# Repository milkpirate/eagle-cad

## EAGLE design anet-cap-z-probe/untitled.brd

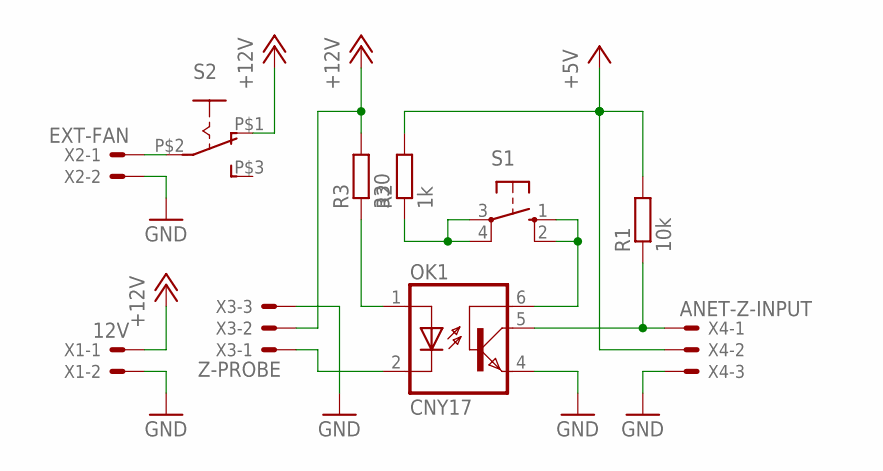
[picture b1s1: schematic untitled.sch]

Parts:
OK1: CNY17; DIL06
R1: 10k; M0805
R2: 1k; M0805
R3: 330; M0805
S1: 10-XX; B3F-10XX
S2: EG1218THIN; THIN
X1: 12V; JST-XH-02-PACKAGE-LONG-PAD
X2: EXT-FAN; JST-XH-02-PACKAGE-LONG-PAD
X3: Z-PROBE; JST-XH-03-PACKAGE-LONG-PAD
X4: ANET-Z-INPUT; JST-XH-03-PACKAGE-LONG-PAD

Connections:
+5V: R1.2, R2.2, X4.2
+12V: R3.2, S2.P$1 (O), X1.1, X3.2
GND: OK1.4 (EMI), X1.2, X2.2, X3.3, X4.3
unnamed: S2.P$2, X2.1
unnamed: OK1.5 (COL), R1.1, X4.1
unnamed: R2.1, S1.3, S1.4 (P1)
unnamed: OK1.6 (BAS), S1.1 (S), S1.2 (S1)
unnamed: OK1.1 (A), R3.1
unnamed: OK1.2 (C), X3.1

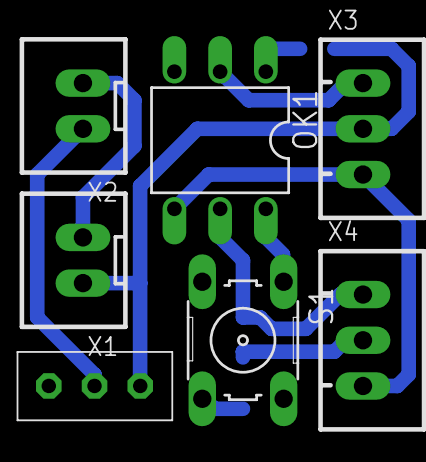
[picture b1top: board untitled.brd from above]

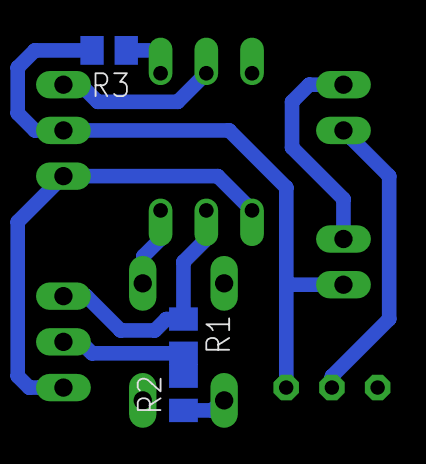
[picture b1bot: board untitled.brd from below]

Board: 2 copper layers, 10 parts (3 on the bottom side), 9 nets.

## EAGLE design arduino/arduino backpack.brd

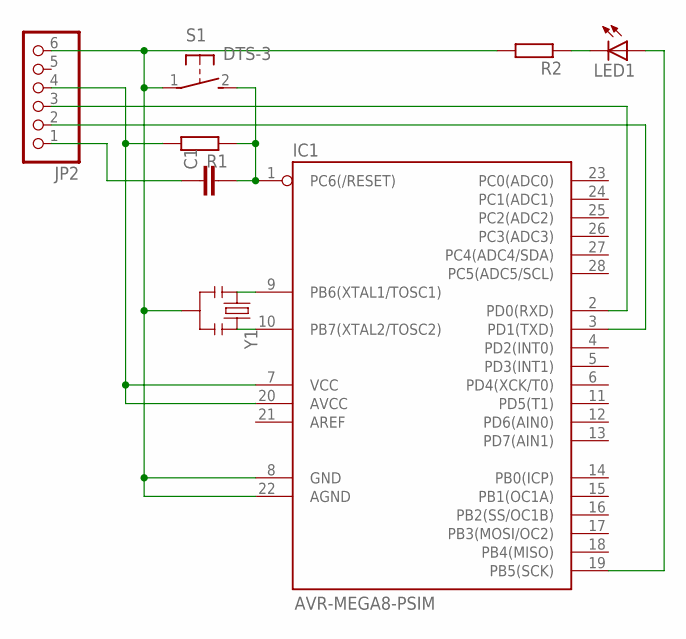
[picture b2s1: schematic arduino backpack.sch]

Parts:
C1: C-EU025-025X050; C025-025X050
IC1: AVR-MEGA8-PSIM; DIL28-3-SIMON
JP2: PINHD-1X6; 1X06
LED1: LED3MM
R1, R2: R-EU_0204/2V; 0204V
S1: DTS-3
Y1: RESONATORPTH; RESONATOR-PTH

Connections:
unnamed: IC1.8 (GND), IC1.22 (AGND), JP2.6, R2.2, S1.1, Y1.2
unnamed: IC1.7 (VCC), IC1.20 (AVCC), JP2.4, R1.2
unnamed: IC1.2 (PD0(RXD)), JP2.3
unnamed: IC1.3 (PD1(TXD)), JP2.2
unnamed: C1.1, JP2.1
unnamed: C1.2, IC1.1 (PC6(/RESET)), R1.1, S1.2
unnamed: IC1.9 (PB6(XTAL1/TOSC1)), Y1.1
unnamed: IC1.10 (PB7(XTAL2/TOSC2)), Y1.3
unnamed: LED1.K (C), R2.1
unnamed: IC1.19 (PB5(SCK)), LED1.A

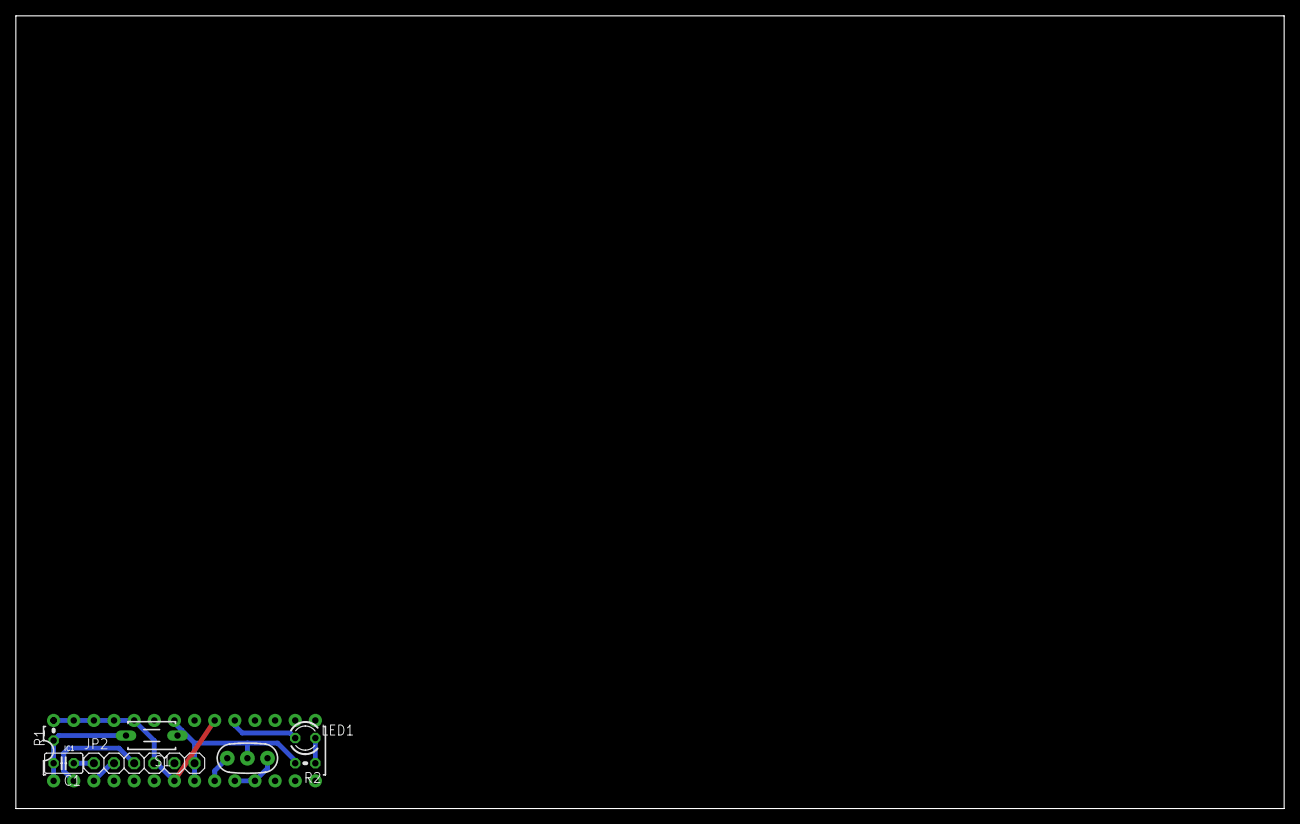
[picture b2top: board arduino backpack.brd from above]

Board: 2 copper layers, 160.0 x 100.0 mm, 8 parts (0 on the bottom side), 10 nets.

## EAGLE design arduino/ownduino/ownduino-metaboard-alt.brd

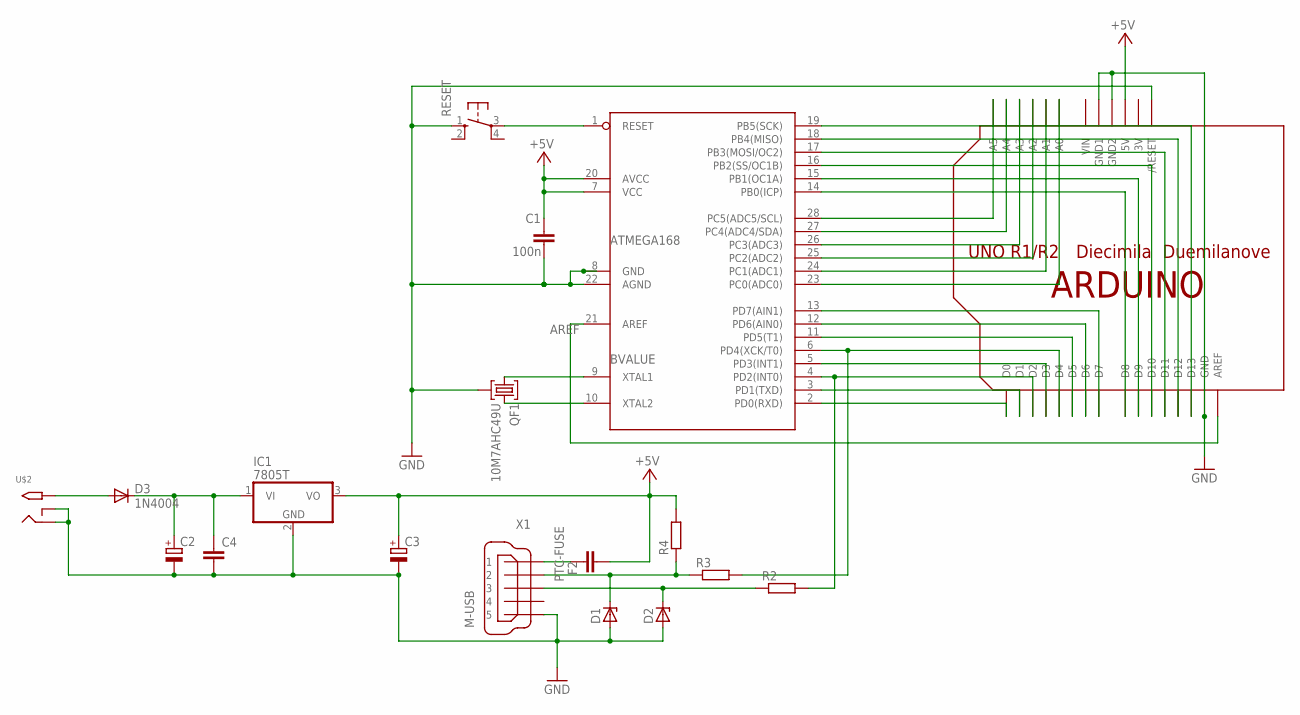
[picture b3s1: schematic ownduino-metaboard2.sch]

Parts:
BVALUE: ATMEGA168; DIL28-3
C1: 100n; C025-024X044
C2, C3: CPOL-EUE5-8.5; E5-8,5
C4: C-EU025-025X050; C025-025X050
D1: ZENER-DIODEZD-7.5; ZDIO-7.5
D2: ZENER-DIODEZD-5; ZDIO-5
D3: 1N4004; DO41-10
F2: PTC-FUSE; C025_050-025X075
IC1: 7805T; TO220H
QF1: 10M7AHC49U; HC49U
R2: R-EU_0207/12; 0207/12
R3, R4: R-EU_0207/10; 0207/10
RESET: 10-XX; B3F-10XX
U$1: ARDUINOUNO; ARDUINO
U$2: 2.1MMJACKTHM; PJ-102A
X1: M-USB; 32005-601

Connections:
3V: U$1.3V
+5V: BVALUE.7 (VCC), BVALUE.20 (AVCC), C1.1, C3.+, F2.1, IC1.3 (VO), R4.2, U$1.5V
A0: BVALUE.23 (PC0(ADC0)), U$1.A0
A1: BVALUE.24 (PC1(ADC1)), U$1.A1
A2: BVALUE.25 (PC2(ADC2)), U$1.A2
A3: BVALUE.26 (PC3(ADC3)), U$1.A3
A4: BVALUE.27 (PC4(ADC4/SDA)), U$1.A4
A5: BVALUE.28 (PC5(ADC5/SCL)), U$1.A5
AREF: BVALUE.21 (AREF), U$1.AREF
D0: BVALUE.2 (PD0(RXD)), U$1.D0
D1: BVALUE.3 (PD1(TXD)), U$1.D1
D2: BVALUE.4 (PD2(INT0)), R2.2, U$1.D2
D3: BVALUE.5 (PD3(INT1)), U$1.D3
D4: BVALUE.6 (PD4(XCK/T0)), R3.2, U$1.D4
D5: BVALUE.11 (PD5(T1)), U$1.D5
D6: BVALUE.12 (PD6(AIN0)), U$1.D6
D7: BVALUE.13 (PD7(AIN1)), U$1.D7
D8: BVALUE.14 (PB0(ICP)), U$1.D8
D9: BVALUE.15 (PB1(OC1A)), U$1.D9
D10: BVALUE.16 (PB2(SS/OC1B)), U$1.D10
D11-MOSI: BVALUE.17 (PB3(MOSI/OC2)), U$1.D11
D12-MISO: BVALUE.18 (PB4(MISO)), U$1.D12
D13-SCK: BVALUE.19 (PB5(SCK)), U$1.D13
D+: D2.C, R2.1, X1.3
D-: D1.C, R3.1, R4.1, X1.2
GND: BVALUE.8 (GND), BVALUE.22 (AGND), C1.2, C2.-, C3.-, C4.2, D1.A, D2.A, IC1.2 (GND), QF1.2, RESET.1 (S), U$1.GND, U$1.GND1, U$1.GND2, U$1.RESET (/RESET), U$2.RING, U$2.RING_SW, X1.5
unnamed: BVALUE.1 (RESET), RESET.3
unnamed: C2.+, C4.1, D3.C, IC1.1 (VI)
unnamed: D3.A, U$2.TIP
unnamed: BVALUE.9 (XTAL1), QF1.1
unnamed: BVALUE.10 (XTAL2), QF1.3
unnamed: F2.2, X1.1
VIN: U$1.VIN

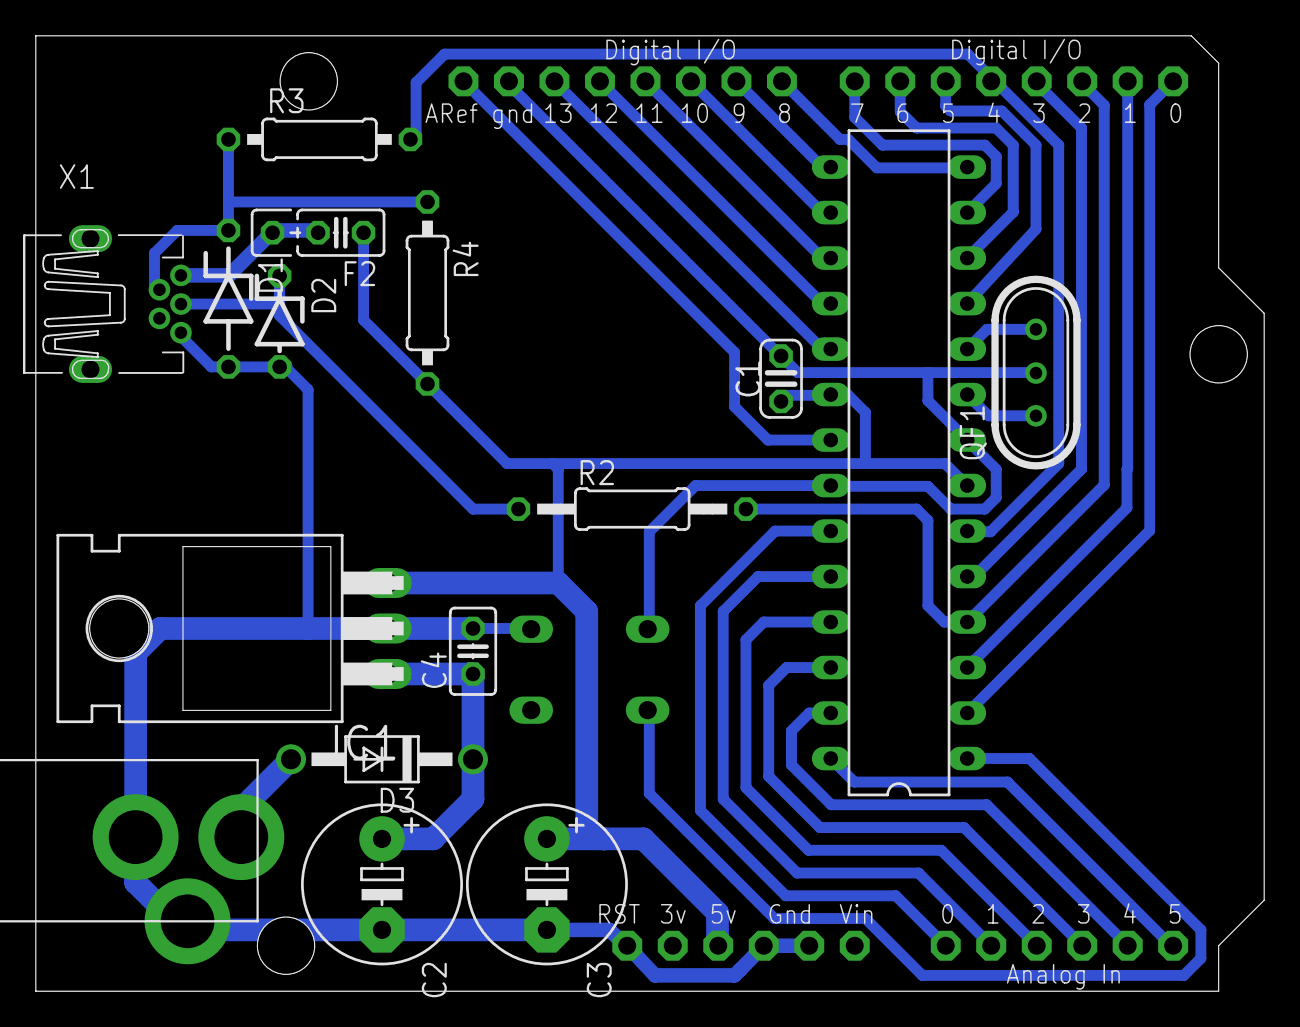
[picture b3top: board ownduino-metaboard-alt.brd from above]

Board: 2 copper layers, 68.6 x 53.3 mm, 18 parts (1 on the bottom side), 31 nets.

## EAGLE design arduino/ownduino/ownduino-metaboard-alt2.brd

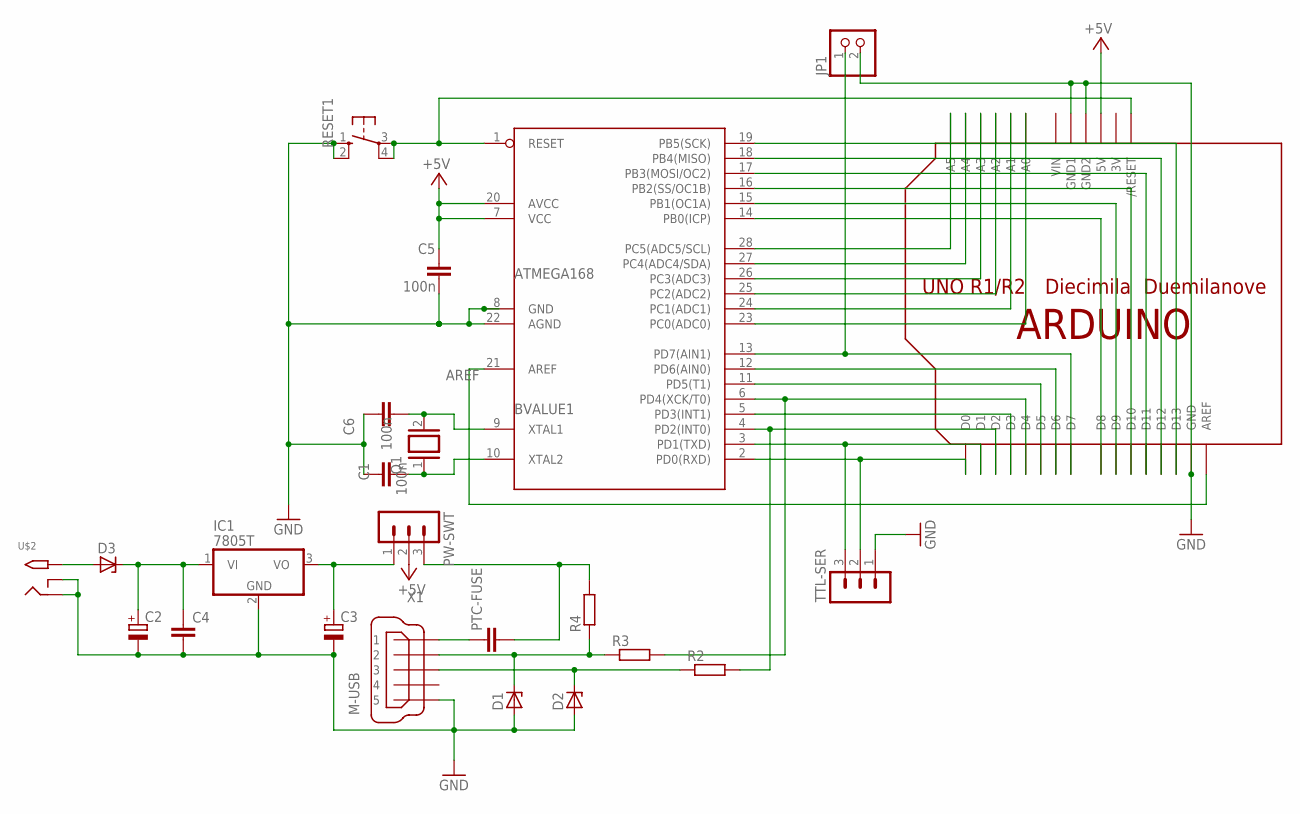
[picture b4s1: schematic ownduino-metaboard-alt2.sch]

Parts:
BVALUE1: ATMEGA168; DIL28-3
C1, C5, C6: 100n; C025-024X044
C2, C3: CPOL-EUE2.5-6; E2,5-6
C4: C-EU025-025X050; C025-025X050
D1, D3: ZENER-DIODEZD-7.5; ZDIO-7.5
D2: ZENER-DIODEZD-5; ZDIO-5
IC1: 7805T; TO220H
JP1: PINHD-1X2; 1X02
PTC-FUSE: C-EU025_050-025X075; C025_050-025X075
PW-SWT: MA03-1
Q1: XTAL/S; QS
R2: R-EU_0207/12; 0207/12
R3, R4: R-EU_0207/10; 0207/10
RESET1: 10-XX; B3F-10XX
TTL-SER: MA03-1
U$1: ARDUINOUNO; ARDUINO
U$2: 2.1MMJACKTHM; PJ-102A
X1: M-USB; 32005-601

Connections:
3V: U$1.3V
+5V: BVALUE1.7 (VCC), BVALUE1.20 (AVCC), C5.1, PW-SWT.2, U$1.5V
A0: BVALUE1.23 (PC0(ADC0)), U$1.A0
A1: BVALUE1.24 (PC1(ADC1)), U$1.A1
A2: BVALUE1.25 (PC2(ADC2)), U$1.A2
A3: BVALUE1.26 (PC3(ADC3)), U$1.A3
A4: BVALUE1.27 (PC4(ADC4/SDA)), U$1.A4
A5: BVALUE1.28 (PC5(ADC5/SCL)), U$1.A5
AREF: BVALUE1.21 (AREF), U$1.AREF
D0: BVALUE1.2 (PD0(RXD)), TTL-SER.2, U$1.D0
D1: BVALUE1.3 (PD1(TXD)), TTL-SER.3, U$1.D1
D2: BVALUE1.4 (PD2(INT0)), R2.2, U$1.D2
D3: BVALUE1.5 (PD3(INT1)), U$1.D3
D4: BVALUE1.6 (PD4(XCK/T0)), R3.2, U$1.D4
D5: BVALUE1.11 (PD5(T1)), U$1.D5
D6: BVALUE1.12 (PD6(AIN0)), U$1.D6
D7: BVALUE1.13 (PD7(AIN1)), JP1.1, U$1.D7
D8: BVALUE1.14 (PB0(ICP)), U$1.D8
D9: BVALUE1.15 (PB1(OC1A)), U$1.D9
D10: BVALUE1.16 (PB2(SS/OC1B)), U$1.D10
D11-MOSI: BVALUE1.17 (PB3(MOSI/OC2)), U$1.D11
D12-MISO: BVALUE1.18 (PB4(MISO)), U$1.D12
D13-SCK: BVALUE1.19 (PB5(SCK)), U$1.D13
D+: D2.C, R2.1, X1.3
D-: D1.C, R3.1, R4.1, X1.2
GND: BVALUE1.8 (GND), BVALUE1.22 (AGND), C1.1, C2.-, C3.-, C4.2, C5.2, C6.1, D1.A, D2.A, IC1.2 (GND), JP1.2, RESET1.1 (S), RESET1.2 (S1), TTL-SER.1, U$1.GND, U$1.GND1, U$1.GND2, U$2.RING, U$2.RING_SW, X1.5
unnamed: C3.+, IC1.3 (VO), PW-SWT.1
unnamed: C2.+, C4.1, D3.C, IC1.1 (VI)
unnamed: D3.A, U$2.TIP
unnamed: BVALUE1.9 (XTAL1), C6.2, Q1.2
unnamed: BVALUE1.10 (XTAL2), C1.2, Q1.1
unnamed: PTC-FUSE.2, PW-SWT.3, R4.2
unnamed: BVALUE1.1 (RESET), RESET1.3, RESET1.4 (P1), U$1.RESET (/RESET)
unnamed: PTC-FUSE.1, X1.1
VIN: U$1.VIN

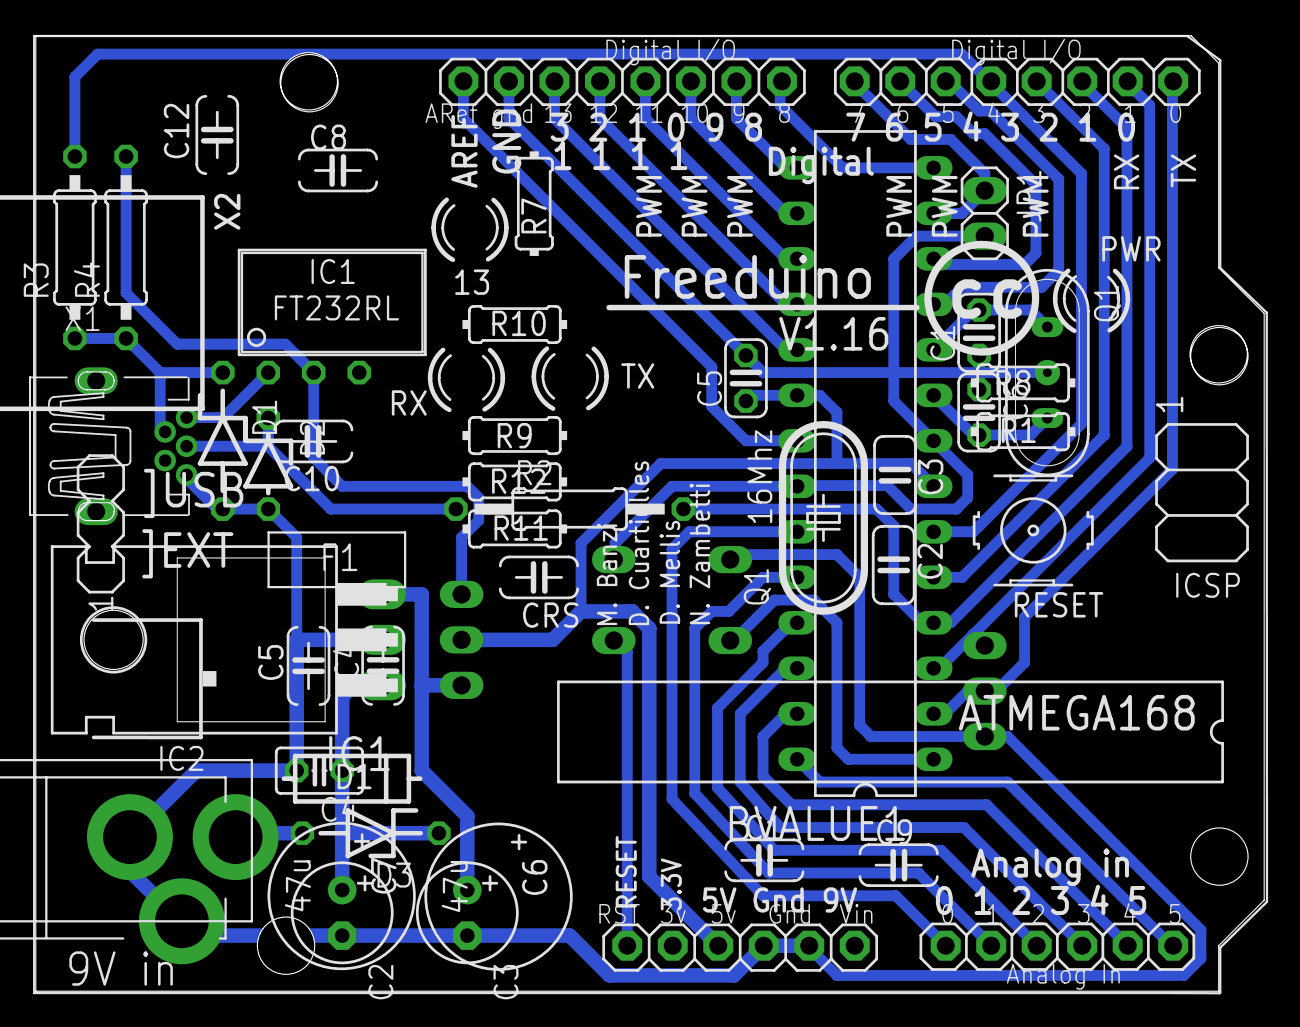
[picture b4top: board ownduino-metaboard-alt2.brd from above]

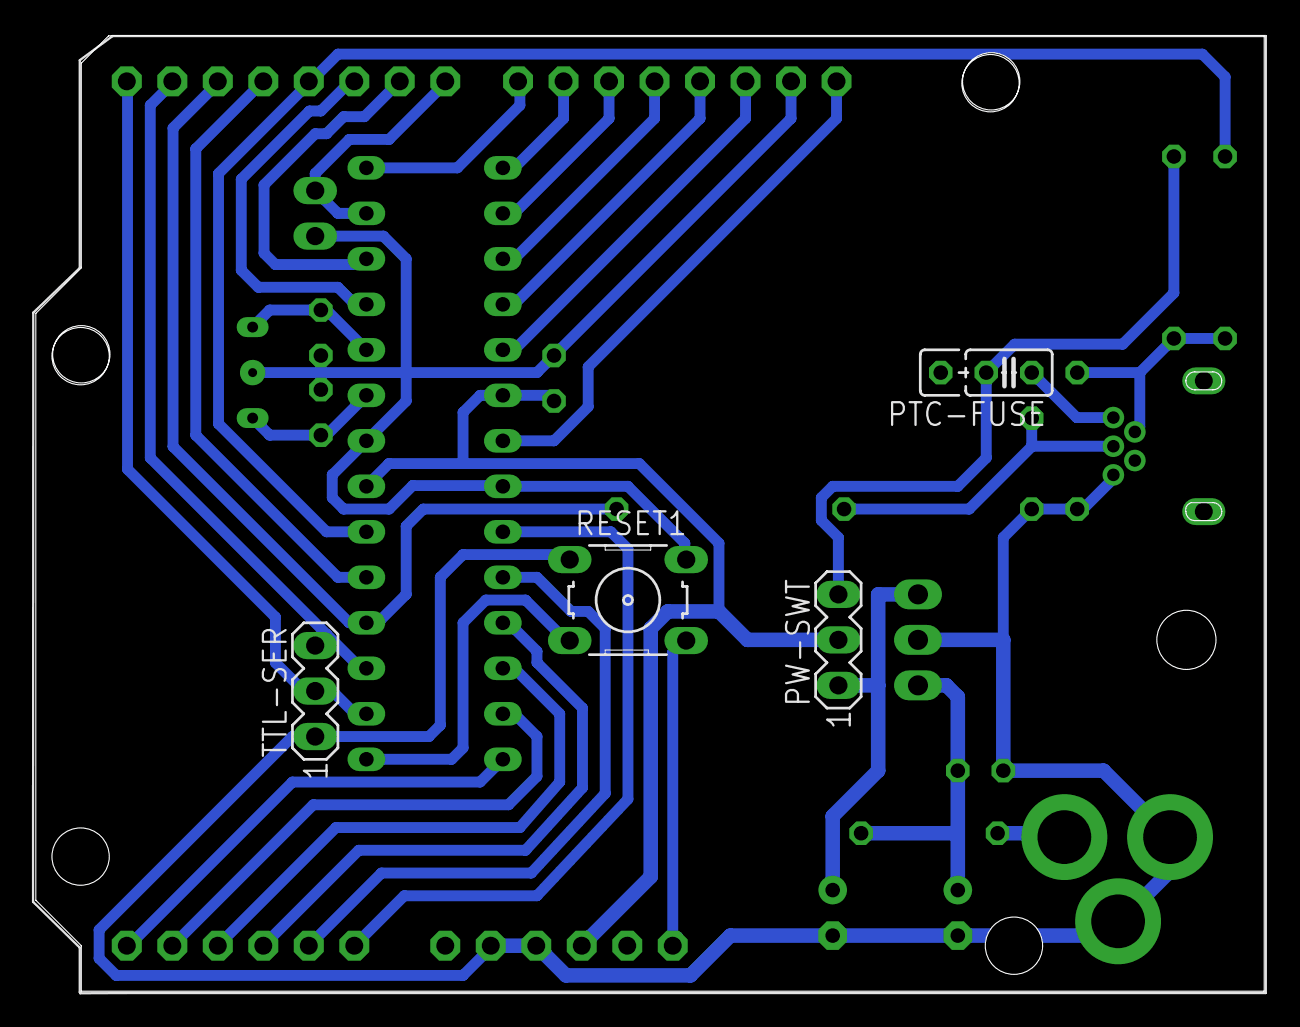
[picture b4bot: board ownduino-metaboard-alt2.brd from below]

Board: 2 copper layers, 68.6 x 53.3 mm, 23 parts (4 on the bottom side), 33 nets.

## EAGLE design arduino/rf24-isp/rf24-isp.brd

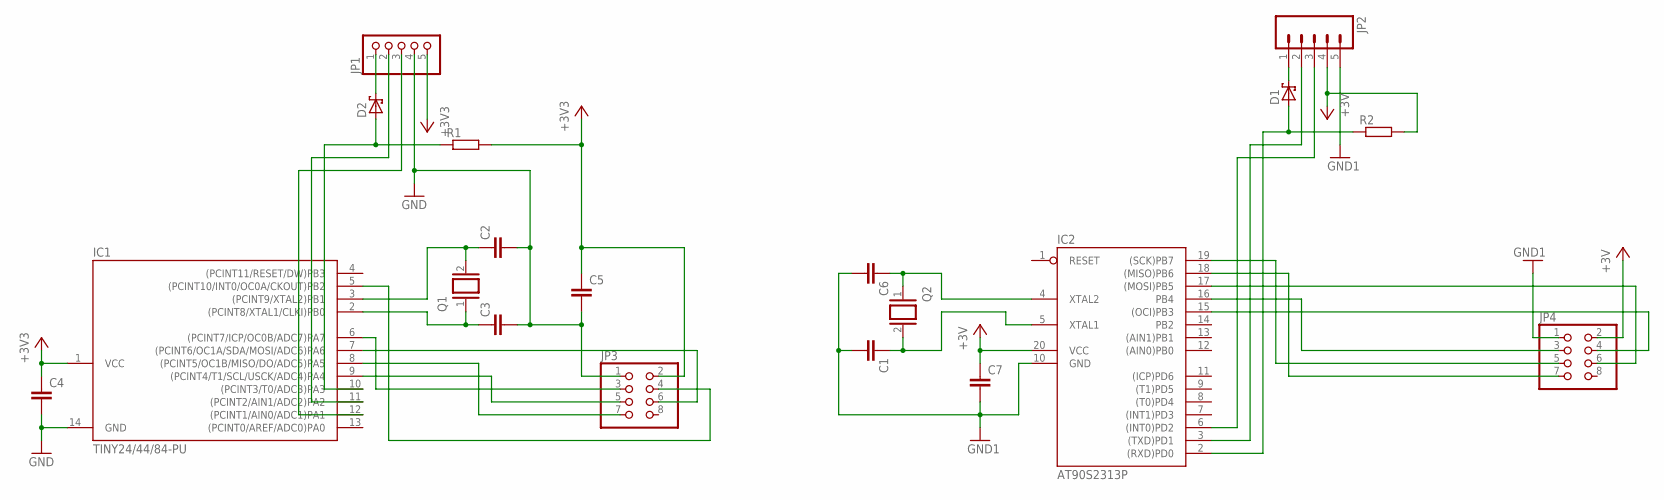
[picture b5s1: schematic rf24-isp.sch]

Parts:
C1, C2, C3, C4, C5, C6, C7: C-EU025-025X050; C025-025X050
D1, D2: SCHOTTKY-DIODETO92H; TO92H
IC1: TINY24/44/84-PU; DIL14
IC2: AT90S2313P; DIL20
JP1: PINHD-1X5; 1X05
JP2: M05PTH; 1X05
JP3, JP4: PINHD-2X4; 2X04
Q1, Q2: XTAL/S; QS
R1: R-EU_0207/12; 0207/12
R2: R-EU_0207/2V; 0207/2V

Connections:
+3V3: C4.1, C5.1, C7.1, IC1.1 (VCC), IC2.20 (VCC), JP1.5, JP2.4, JP3.2, JP4.2, R1.2, R2.2
GND: C1.2, C2.2, C3.2, C4.2, C5.2, C6.2, C7.2, IC1.14 (GND), IC2.10 (GND), JP1.4, JP2.5, JP3.1, JP4.1
unnamed: C2.1, IC1.3 ((PCINT9/XTAL2)PB1), Q1.2
unnamed: C3.1, IC1.2 ((PCINT8/XTAL1/CLKI)PB0), Q1.1
unnamed: D2.2 (C), JP1.1
unnamed: IC1.7 ((PCINT6/OC1A/SDA/MOSI/ADC6)PA6), JP3.6
unnamed: IC1.6 ((PCINT7/ICP/OC0B/ADC7)PA7), JP3.3
unnamed: IC1.9 ((PCINT4/T1/SCL/USCK/ADC4)PA4), JP3.5
unnamed: IC1.8 ((PCINT5/OC1B/MISO/DO/ADC5)PA5), JP3.7
unnamed: IC1.5 ((PCINT10/INT0/OC0A/CKOUT)PB2), JP3.4
unnamed: IC2.16 (PB4), JP4.3
unnamed: D1.2 (C), JP2.1
unnamed: IC2.19 ((SCK)PB7), JP4.5
unnamed: IC2.18 ((MISO)PB6), JP4.7
unnamed: IC2.17 ((MOSI)PB5), JP4.6
unnamed: IC2.15 ((OCI)PB3), JP4.4
unnamed: C1.1, IC2.5 (XTAL1), Q2.2
unnamed: C6.1, IC2.4 (XTAL2), Q2.1
RST0: IC1.12 ((PCINT1/AIN0/ADC1)PA1), JP1.3
RST1: IC2.6 ((INT0)PD2), JP2.3
RX0: IC1.11 ((PCINT2/AIN1/ADC2)PA2), JP1.2
RX1: IC2.3 ((TXD)PD1), JP2.2
TX: D2.1 (A), IC1.10 ((PCINT3/T0/ADC3)PA3), R1.1
TX1: D1.1 (A), IC2.2 ((RXD)PD0), R2.1

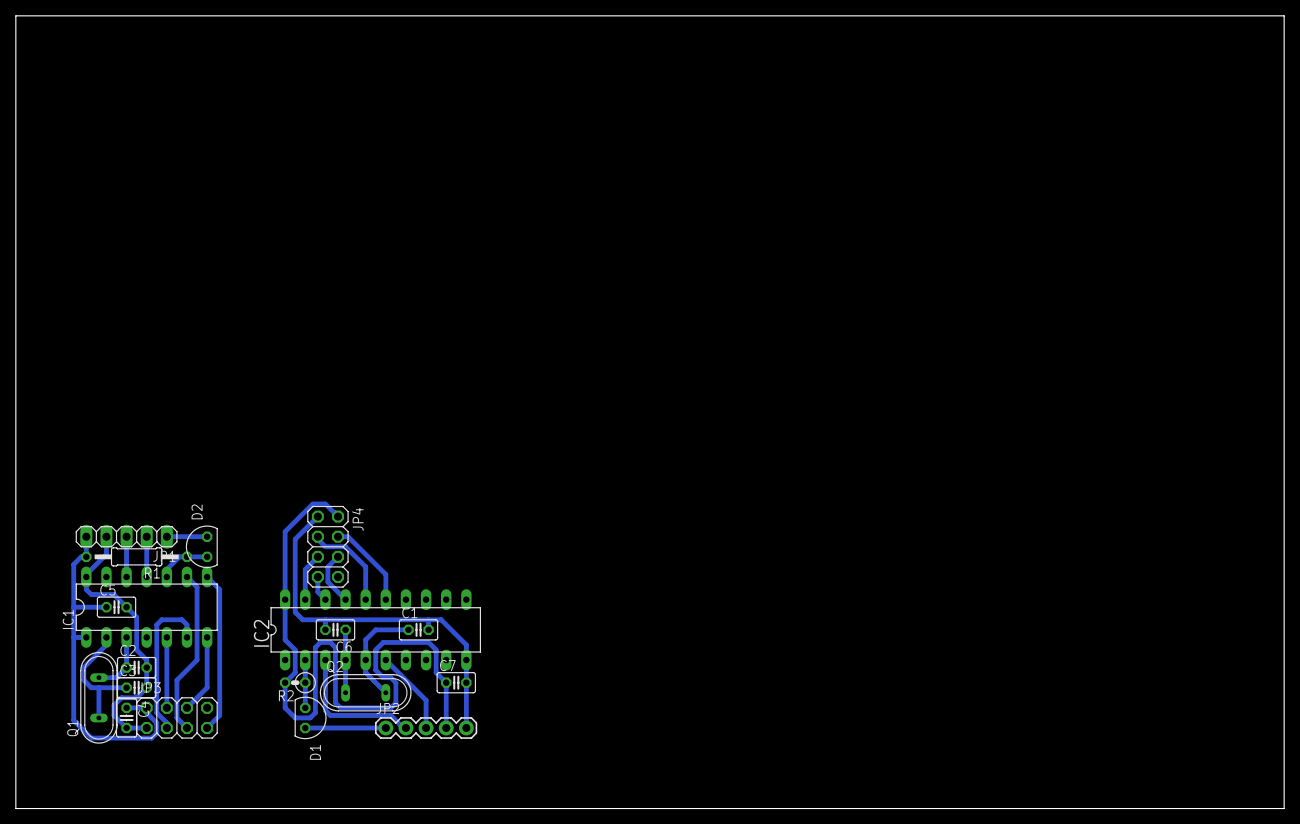
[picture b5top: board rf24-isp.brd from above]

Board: 2 copper layers, 160.0 x 100.0 mm, 19 parts (0 on the bottom side), 24 nets.

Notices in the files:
parts and their libraries:
SparkFun-FreqCtrl: Licensing: Creative Commons ShareAlike 4.0 International - https://creativecommons.org/licenses/by-sa/4.0
SparkFun: Licensing: CC v3.0 Share-Alike You are welcome to use this library for commercial purposes.
